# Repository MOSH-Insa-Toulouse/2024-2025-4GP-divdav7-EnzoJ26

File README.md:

2024-2025-4GP-HILLAH-JACQUET
---
## Sommaire 
   - [I) Contexte et objectifs du projet](#I-Contexteetobjectifsduprojet)
   - [II) Capteur à base de crayon graphite](#II-Capteuràbasedecrayongraphite)
   - [III) Electronique Analogique](#III-Electroniqueanalogique)
   - [IV) KiCad et PCB](#IV-KiCadetPCB)
   - [V) Arduino](#V-Arduino)
   - [VI) Application Mobile](#VI-ApplicationMobile)
   - [VII) Banc de Test](#VII-BancdeTest)
   - [VIII) Datasheet](#VIII-Datasheet)

---

## I) Contexte et objectifs du projet

L'objectif de ce projet est de réaliser un capteur low-tech à base de graphite sachant que les recherches ont démontré les nombreux avantages de l'utilisation de ce matériau. L’électronique à base de papier gagne en popularité parmi les ingénieurs grâce à sa facilité d’approvisionnement, sa simplicité de fabrication et son faible coût.<br>
Pour ce faire, nous avons mis en place la réalisation de tous les processus de fabrication d'un shield PCB que nous avons ensuite connecté à une carte Arduino.<br>
Notre PCB contient 6 composants différents : une jauge de contrainte, un flex sensor, un écran oled, un encodeur rotatoire, un potentiomètre digital et un module Bluetooth. À noter que nous n'avons pas utilisé le servo-moteur qui faisait partie des composants disponibles à implémenter.<br>
La carte Arduino fonctionne avec un code que nous avons implémenté en s'inspirant grandement des codes qui étaient disponibles en open-source.<br>
Nous avons ensuite réalisé une application mobile connectée au module bluetooth afin d'acquérir les données renvoyées par nos capteurs sur le téléphone.<br>
Nous avons évalué le capteur sur un banc de test avant de conclure par la datasheet de notre capteur.<br>
À la fin de la lecture de ce github, vous devriez savoir quel capteur choisir entre le graphite et le flex ;) . <br>

# Livrables

- PCB shield pour arduino uno <br>
- Code arduino <br>
- Banc de test du capteur <br>
- Application android qui fonctionne par bluetooth <br>
- Datasheet <br>

# Matériel utilisé

-Résistances: 1x1kΩ, 1x10kΩ, 2x100 kΩ, 1x47kΩ <br>
-Potentiomètre digital MCP41050 <br>
-Capacités: 3x100nF et 1x1µF <br>
-Arduino Uno <br>
-Capteur graphite à partir d'un support papier et d'un crayon <br>
-Flex Sensor <br>
-Encodeur rotatoire Keyes KY-040 <br>
-Ecran OLED 128x64 <br>
-Module Bluetooth HC-05 <br>
-Amplificateur opérationnel LTC1050 <br>

## II) Capteur à base de crayon graphite

Ce capteur low-tech utilise la théorie de la percolation au sein d’un système granulaire constitué de nanoparticules de graphite.<br>
Nous déposons une fine couche de graphite sur la feuille de papier ce qui présente un réseau percolé caractéristique. Dans ce réseau, le transport des électrons entre les nanoparticules est basé sur le mécanisme de l’effet tunnel.<br>
Lors de l'application de déformations en tension, le réseau percolé se trouve directement étendu. Cette déformation entraîne une augmentation de la distance effective entre les particules de graphite au sein du réseau. Une partie des chemins de percolation sont par conséquent rompus. Ainsi, la conduction du matériau diminue, donc la résistance de la couche de graphite augmente.<br>
Inversement, lors de l’application de déformations en compression, le réseau percolé se trouve directement comprimé. Cette déformation entraîne une diminution de la distance effective entre les particules.<br> 
Ainsi, de nouveaux chemins de percolation sont créés, la conduction du matériau augmente, soit la résistance de la couche de graphite diminue.

Voici un schéma explicatif de ces phénomènes:

<p align="center">

<br>
<i>Sensibilité et Résistance en fonction de la dureté des mines</i>
</p>

Une jauge de contrainte est un circuit résistif dont la résistance varie en fonction de sa déformation. Donc en mesurant les variations de résistance de la jauge, nous en avons déduit la contrainte et la déformation appliquées.<br>
Notre jauge de contrainte est alimentée par une tension régulée de 5V d'une carte Arduino UNO.
<br>
Voici ci dessous le schéma d'un modèle de capteur graphite. Dans notre projet, nous avons utilisé les crayons de dureté 2H ; 2B ; HB.

<p align="center">

<br>
<i>Capteur à jauge de contrainte à base de crayon graphite</i>
</p>

## III) Electronique Analogique

Ce capteur graphite possède une résistance variable de l'ordre du GΩ. Le courant généré lorsque l'on applique une tension de 5V aux bornes du capteur est très faible.<br>
Pour obtenir un signal exploitable nous devions l'amplifier. Pour ce faire, nous avons utilisé un montage transimpédance constitué d'un amplificateur opérationnel.<br>
Pour cela nous avons dans un premier temps effectué une simulation électronique du capteur et de ce montage transimpédance sous LTSpice. Voici ci-dessous le montage réalisé sous LTSpice. Pour notre montage nous avons choisi l'AOP LTC1050 prenant en entrée un courant faible (de l'ordre d'une dizaine de picoampère).

<p align="center">

<br>
<i>Circuit amplificateur réalisé dans LTSpice</i>
</p>
<br>
Ce circuit amplificateur contient 3 filtres passe bas passifs, dont nous avons pu tester le bon fonctionnement.<br>
<br>
- Le premier étage a une fréquence de coupure de 16 Hz, il permet de filtrer les bruits du courant en entrée. Nous avons testé ce premier étage pour vérifier que la fréquence de coupure soit la bonne.
<br>
</p>

<p align="center">

<br>
<i>Simulation de l'étage 1 dans LTSpice</i>
</p>
En effet la fréquence de coupure est la bonne.
<br>
- Le second étage a une fréquence de coupure de 1,6 Hz. Il permet de filtrer la composante de bruit du réseau électrique: le bruit à 50 Hz.
<br>
</p>
<p align="center">

<br>
<i>Simulation de l'étage 2 dans LTSpice</i>
</p>
La fréquence de coupure est de 2,1Hz alors que celle attendue est de 1,6Hz, ce qui reste dans les plages de fréquences attendues, donc nous la validons.
<br>
- Le dernier étage a une fréquence de coupure à 1,6 kHz qui permet d'atténuer le bruit provenant lors du traitement électronique.
<br>
</p>
<p align="center">

<br>
<i>Simulation de l'étage 3 dans LTSpice</i>
</p>
En effet la fréquence de coupure est la bonne.
<br> 
Cette simulation nous permet de confirmer que l’arduino pourra bel et bien mesurer le signal de sortie car il sera d’environ 1V.

## IV) KiCad et PCB

Avant d'imprimer le PCB et de souder nos différents composants, nous avons dessiné les schémas électroniques, réalisé les composants électroniques et créé le PCB sur KICAD. Cette étape est importante car elle permet de prévisualiser le PCB, vérifier que tous les composants tiennent sur le PCB et ainsi de le sortir. Elle permet également de créer les différents routages de pistes. 

<p align="center">

<br>
<i>Schémas électroniques</i>
</p>

<p align="center">

<br>
<i>Création du PCB et des différentes empreintes sur KiCad</i>
</p>

<p align="center">

<br>
<i>Visualisation 3D du PCB (idéale)</i>
</p>
<br>
Lorsque la disposition de nos différents composants électroniques était terminée suite au routage des pistes, nous avons pu imprimer le PCB, le percer et y souder les différents composants.
<br>
<br>
<p align="center">

<br>
<i>PCB terminé</i>
</p>

Nous avons rencontré des problèmes lors de cette étape qui représentait une étape très importante du projet. Les librairies étaient assez complexes à retrouver et comme elles contenaient nos différentes empreintes cela nous a posé pas mal de problèmes dans notre gestion du temps, mais également dans la difficulté que l'on a éprouvé à en refaire.<br>
Au niveau du routage, il fallait optimiser la place présente sur le PCB tout en choisissant stratégiquement l'emplacement des différents modules. Cela n'a pas pu se faire sans la présence de 3 via. La visualisation 3D de notre PCB est bien celle qui découle de notre éditeur de PCB, mais c'était sans compter sur le fait que certains des modules que nous avions avaient leurs broches en déphasage avec les connexions disponibles présentes sur notre PCB (le module Bluetooth a une broche dans le vide et l'écran OLED se connecte de sorte à ne pas laisser la place au Flex Sensor de se connecter sur le PCB directement. Nous avons donc réfléchi à une solution filaire permettant de connecter l'écran OLED tout en le gardant à l'extérieur de la carte). Les autres modules n'ont pas de soucis de connexion.<br>
Nous avons solicité l'aide de Mr Grisolia et de Cathy particulièrement sur la partie empreintes et sur le routage. Nous les remercions de nous avoir débloqué plus d'une fois.

## V) Code Arduino

Le code Arduino permet la réception des mesures faites par les deux capteurs (Graphites et Flex Sensor) et d'afficher ces valeurs sur l'OLED. Pour cela nous nous sommes inspirés des codes disponibles en open-source. Du côté de l'application, bien qu'elle soit fonctionnelle sur la partie connexion au module bluetooth, elle ne trace pas le graphe de la variation de la résistance de nos capteurs en fonction de la déformation. En attendant de pouvoir déboguer le problème lié au code, nous avons donc pu effectuer nos mesures gräce à l'écran OLED et l'encodeur rotationnel qui permet de sélectionner le menu voulu par l'utilisateur. À noter l'utilisation d'un potentiomètre digital qui sert particulièrement à faire varier la valeur de la résistance R2 afin de mieux gérer notre gain. 
Notre programme principal est composé de sous programmes associés à ces éléments (à noter que nous ne nous sommes pas servis du servo-moteur dans ce projet):
<br>
<p align="center">

<br>
<i>Différents modules arduino</i>
<br>   

Les objectifs de la partie Arduino étaient d'acquérir les données de nos capteurs (résistance en fonction de la déformation), d'afficher nos mesures sur l'écran OLED via un menu déroulant contrôlé par l'encodeur et enfin, de communiquer avec l'application créée sous MIT APP Inventor. Ils ont été dans l'ensemble bien remplis.

## VI) Application mobile

Nous avons réalisé une application mobile sur le site MIT APP Inventor. <br>
Une fois que le module bluetooth est connecté au téléphone, nous pouvons acquérir les données des capteurs en temps réel et les tracer sur le graphe. 

<br> 
<p align="center">

<br> 
<i>Aperçu MIT APP Inventor</i>
<br>
<p align="center">

<br> 
<i>Face avant de l'application</i>
<br>
Malgré une application fonctionnelle sur la partie de recherche des périphériques et sur la connexion au HC-05, elle présente des limites sur le tracé de la variation de la résistance de notre capteur en fonction de la déformation qui y est appliquée. Comme détaillé lors de la partie précédente, en attendant de débuguer le problème, nous avons codé l'écran OLED pour qu'il nous affiche les valeurs d'intérêt.
   
## VII) Banc de tests

Nous avons relevé la variation de résistance de notre capteur en fonction de son angle de déformation. Pour cela, nous nous sommes servis de ce modèle de banc de test réalisé au FabLab, possédant pour chaque étage la même épaisseur, mais un diamètre différent. Nous disposions de 5 étages allant de 2 à 4 cm de diamètre avec un pas de 0,5cm entre chaque étage, tous étant épais de 0,2cm.
<br> 
<p align="center">

<br>
<i>Banc de test utilisé</i>
<br>
Les objectifs du banc étaient de pouvoir enregistrer les données, les traiter, les comparer avant de pouvoir concevoir et rédiger notre Datasheet.
   
## VIII) Datasheet

Nous avons déposé le PDF de la datasheet contenant une conclusion sur le choix de nos capteurs en fonction des résultats que nous avions obtenus que nous vous invitons à aller voir. Nous vous alertons sur le fait que nous avons donné un modèle linéaire aux différentes mesures que nous avons obtenu en compression et en tension, malgré le fait que les courbes de base ne soient pas linéaires. Les sensibilités que nous calculons sont obtenues en prenant en compte nos modèles linéaires. <br>

# Contacts
<br>
Si vous avez des questions sur ce projet, n'hésitez pas à contacter notre superbe duo (le binôme de l'année on a dit): 
<br>

David : hillah-a@insa-toulouse.fr
<br>
Enzo : ejacquet@insa-toulouse.fr

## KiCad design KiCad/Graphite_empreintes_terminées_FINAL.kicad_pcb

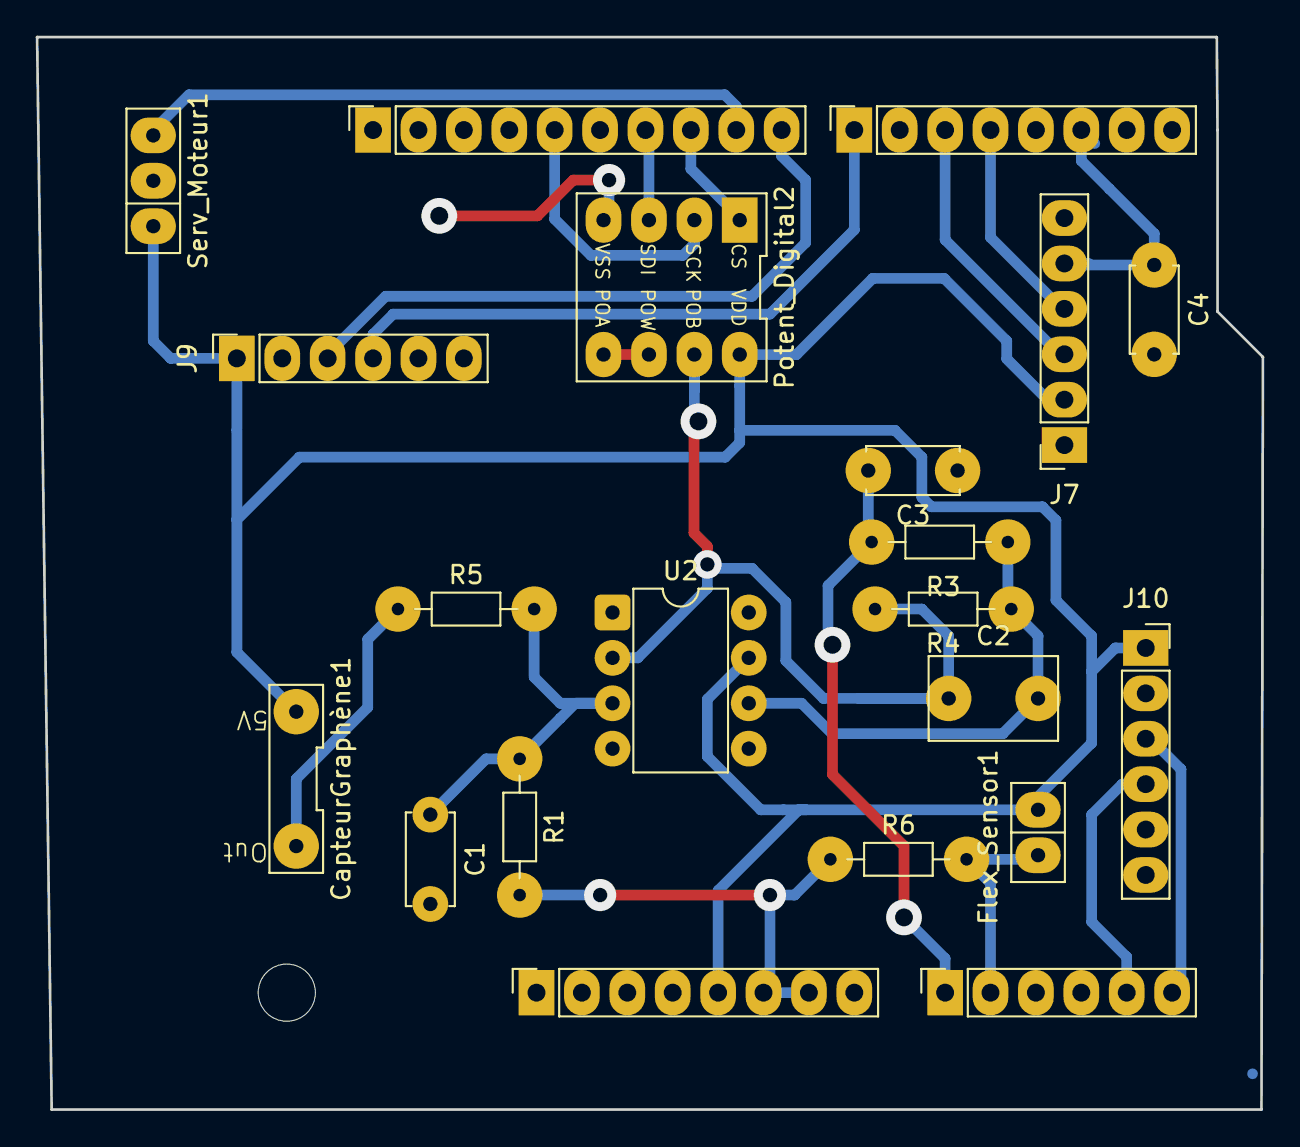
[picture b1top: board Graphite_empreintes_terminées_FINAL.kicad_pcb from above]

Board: 2 copper layers, 68.6 x 60.0 mm, 22 parts (0 on the bottom side), 19 nets.

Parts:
C1, C3: 100n; C_Disc_D5.0mm_W2.5mm_P5.00mm
C2: 1µ; C_Rect_L7.0mm_W4.5mm_P5.00mm
C4: 100n; C_Disc_D4.7mm_W2.5mm_P5.00mm
CapteurGraphène1: capp_graph
Flex_Sensor1: SIP-2
J1: Power; PinSocket_1x08_P2.54mm_Vertical
J2: Digital/PWM; PinSocket_1x10_P2.54mm_Vertical
J3: Analog; PinSocket_1x06_P2.54mm_Vertical
J4: Digital/PWM; PinSocket_1x08_P2.54mm_Vertical
J7: Encodeur1; Bluetooth HC-05
J9: BT1; Bluetooth HC-05
J10: OLED1; Bluetooth HC-05
MH2: MountingHole_3.2mm
Potent_Digital2: Potentiometre_Digital3
R1, R3, R4: 100k; R_Axial_DIN0204_L3.6mm_D1.6mm_P7.62mm_Horizontal
R5, R6: 10k; R_Axial_DIN0204_L3.6mm_D1.6mm_P7.62mm_Horizontal
Serv_Moteur1: Servomoteur
U2: LTC1050CN8; DIP-8_W7.62mm

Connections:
5V: CapteurGraphène1.1 (5V), Flex_Sensor1.1 (5V), J1.5, J7.2 (GND), J9.1 (5V), J10.1 (5V), Potent_Digital2.8 (VDD), Serv_Moteur1.1 (5V), U2.7 (V+)
A1: Flex_Sensor1.2 (A1), J3.2, R6.2
AmpliOut: C3.2, J3.1, R3.2
CLK: C4.1, J4.6, J7.5
CS: J2.8, Potent_Digital2.1 (CS)
DATA: J4.4, J7.4 (Rx)
GND: C1.2, C3.1, C4.2, J1.6, J1.7, J2.4, J7.1 (5V), J9.2 (GND), J10.2 (GND), Potent_Digital2.4 (VSS), Potent_Digital2.5 (POA), Potent_Digital2.6 (POW), R1.2, R6.1, Serv_Moteur1.2 (GND), U2.4 (V-)
unnamed: CapteurGraphène1.2 (Out), R5.1
unnamed: C1.1, R1.1, R5.2, U2.3 (+IN)
unnamed: C2.2, R3.1, R4.1, U2.6 (OUT)
R2: C2.1, Potent_Digital2.7 (POB), R4.2, U2.2 (-IN)
RXD: J4.1, J9.4 (Rx)
SCK: J2.5, Potent_Digital2.2 (SCK)
SCL: J2.1, J3.6, J10.3 (Tx)
SDA: J2.2, J3.5, J10.4 (Rx)
SDI: J2.7, Potent_Digital2.3 (SDI)
SW: J4.3, J7.3 (Tx)
TXD: J2.10, J9.3 (Tx)
Vout_Servo: J2.9, Serv_Moteur1.3 (9)

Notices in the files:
parts and their libraries:
COPYRIGHT: Copyright C 2016 Accelerated Designs. All rights reserved
